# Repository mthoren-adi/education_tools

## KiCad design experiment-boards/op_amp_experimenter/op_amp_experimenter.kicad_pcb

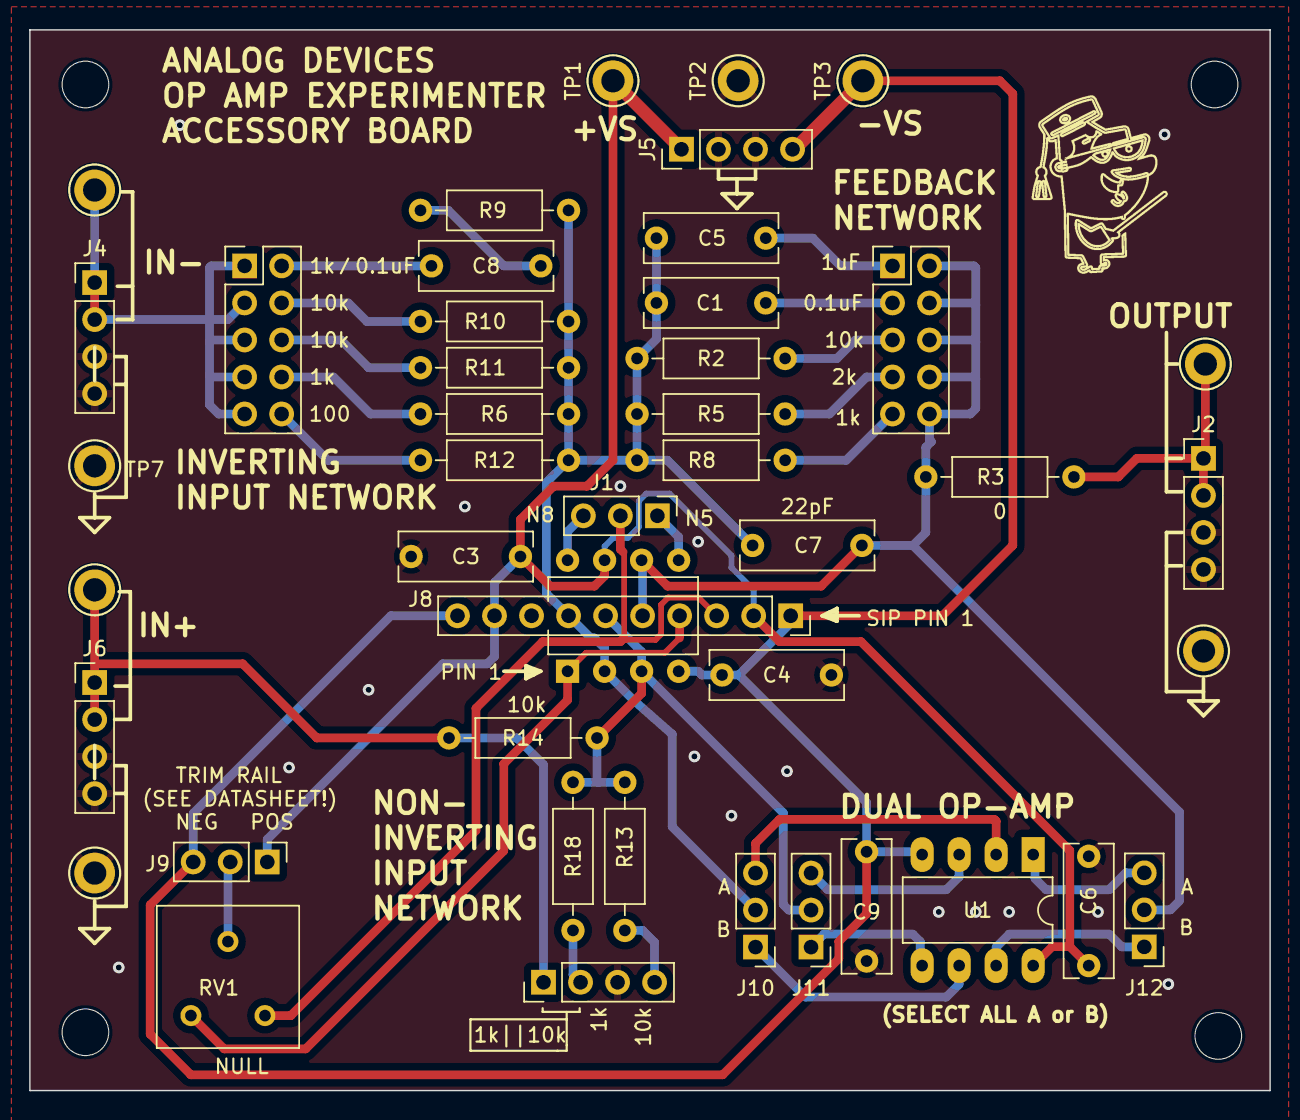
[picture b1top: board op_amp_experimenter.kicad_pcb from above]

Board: 2 copper layers, 85.1 x 72.8 mm, 50 parts (0 on the bottom side), 33 nets.

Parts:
C1, C8: 0.1uF; C_Rect_L9.0mm_W3.2mm_P7.50mm_MKT
C3, C4, C6, C9: 1.0uF; C_Rect_L9.0mm_W3.2mm_P7.50mm_MKT
C5: 1uF; C_Rect_L9.0mm_W3.2mm_P7.50mm_MKT
C7: 22pF; C_Rect_L9.0mm_W3.2mm_P7.50mm_MKT
H1, H2, H3, H4: MountingHole; MountingHole_3.2mm_M3
J1, J9, J10, J11, J12: Conn_01x03_Pin; PinHeader_1x03_P2.54mm_Vertical
J2, J3, J4, J5, J6: Conn_01x04_Pin; PinHeader_1x04_P2.54mm_Vertical
J8: Conn_01x10_Socket; PinSocket_1x10_P2.54mm_Vertical
J14, J15: Conn_02x05_Odd_Even; PinHeader_2x05_P2.54mm_Vertical
R2, R10, R11, R13, R14: 10k; R_Axial_DIN0207_L6.3mm_D2.5mm_P10.16mm_Horizontal
R3: 0; R_Axial_DIN0207_L6.3mm_D2.5mm_P10.16mm_Horizontal
R5: 2k; R_Axial_DIN0207_L6.3mm_D2.5mm_P10.16mm_Horizontal
R6, R8, R9, R18: 1k; R_Axial_DIN0207_L6.3mm_D2.5mm_P10.16mm_Horizontal
R12: 100; R_Axial_DIN0207_L6.3mm_D2.5mm_P10.16mm_Horizontal
RV1: 1k; Potentiometer_Bourns_3386F_Vertical
TP1, TP2, TP3, TP4, TP5, TP6, TP7, TP8, TP9: TestPoint; TestPoint_Keystone_5005-5009_Compact
U1: LM358; DIP-8_W7.62mm_LongPads
U2: LM741; DIP-8_W7.62mm
U$1: PROFF

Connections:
/IN+: J8.6, J11.2, R13.1, R14.2, R18.1, U2.3 (+)
/IN-: C1.1, C5.1, C7.1, J8.7, J10.2, R2.1, R5.1, R6.2, R8.1, R9.2, R10.2, R11.2, R12.2, U2.2 (-)
/NN: J8.4, RV1.3, U2.1 (NULL)
/NP: J1.2, J8.3, RV1.1
/NP1: J1.1, U2.5 (NULL)
/NP2: J1.3, U2.8 (ALT)
/OUT: C7.2, J8.5, J12.2, J15.2, J15.4, J15.6, J15.8, J15.10, R3.1, U2.6
GND: C3.2, C4.1, C6.2, C9.1, J2.3, J2.4, J3.3, J4.3, J4.4, J5.2, J5.3, J6.3, J6.4, TP2.1, TP5.1, TP7.1, TP9.1
unnamed: C8.2, R9.1
unnamed: J2.1, J2.2, R3.2, TP4.1
unnamed: J3.1, J6.1, J6.2, R14.1, TP8.1
unnamed: J3.2, R18.2
unnamed: J3.4, R13.2
unnamed: J9.2, RV1.2
unnamed: J10.1, U1.6 (-)
unnamed: J10.3, U1.2 (-)
unnamed: J11.1, U1.5 (+)
unnamed: J11.3, U1.3 (+)
unnamed: J12.1, U1.7
unnamed: J12.3, U1.1
unnamed: J4.1, J4.2, J14.1, J14.3, J14.5, J14.7, J14.9, TP6.1
unnamed: C8.1, J14.2
unnamed: J14.4, R10.1
unnamed: J14.6, R11.1
unnamed: J14.8, R6.1
unnamed: J14.10, R12.1
unnamed: C5.2, J15.1
unnamed: C1.2, J15.3
unnamed: J15.5, R2.2
unnamed: J15.7, R5.2
unnamed: J15.9, R8.2
VCC: C3.1, C6.1, J5.1, J8.2, J8.9, J9.1, TP1.1, U1.8 (V+), U2.7 (V+)
VSS: C4.2, C9.2, J5.4, J8.1, J8.10, J9.3, TP3.1, U1.4 (V-), U2.4 (V-)

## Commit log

2018-12-07 Initial commit for efficiency lab.
2018-12-07 Add comments
2018-12-09 Move ammeter to the correct location.
2021-05-04 Adding wein bridge oscillator circuit
2023-08-05 Add You Build It 45W Power Supply LTspice and Eagle files.
2023-10-14 Initial release
    This is the inital release of the first 5 m1k accessory PC boards.
2023-10-14 Add single amplifier buffer board
    Intial release of the single amplifier input buffer board.
    Initial release of the transistor op-amp experimant board
2023-10-14 Add Eagle files for SIP version of discrete op-amp
2023-10-14 add more boards
    Design files etc. added for LTC1043 based analog mux board and adjustable pot voltagedivider board
2023-10-14 Adding more board files
    Adding cad files for lumped LC trnasmission line board.
2023-10-14 modify header spacing
    Moved the analog mux input header on to 0.1" grid centers
2023-10-14 Adding more board files
    Adding more accessory board files to the inventory
2023-10-14 Add some M2k boards
    Add CAD files for 2 M2k analog Mux boards and CAD files for M2k Breadboard adapter
2023-10-21 Put accessory boards in directories. Add LTspice. Add gerbers. Add 45W power supply.
2024-02-09 Adding flip-flop experiment simulations
